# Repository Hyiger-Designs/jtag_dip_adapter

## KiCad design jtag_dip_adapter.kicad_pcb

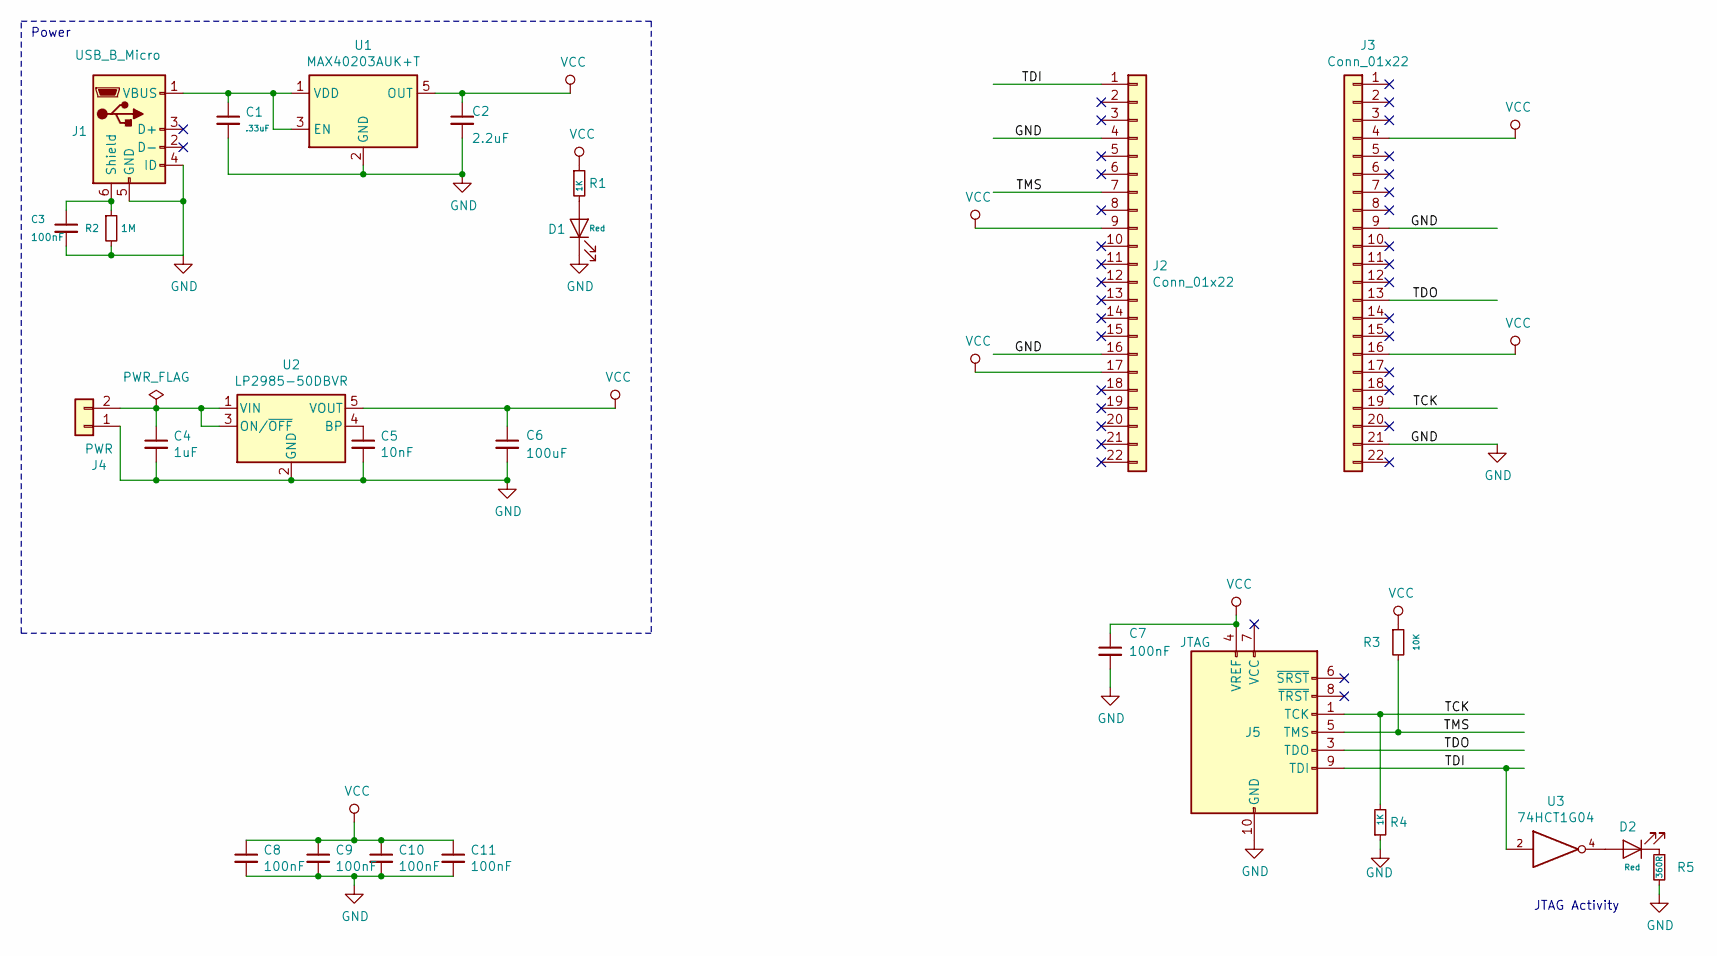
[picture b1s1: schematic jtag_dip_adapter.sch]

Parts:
C1: .33uF; C_0603_1608Metric_Pad1.05x0.95mm_HandSolder; MPN JMK107B7474KA-T
C2: 2.2uF; C_0603_1608Metric_Pad1.05x0.95mm_HandSolder; MPN C0603C225K8RACTU
C3: 100nF; C_0603_1608Metric_Pad1.05x0.95mm_HandSolder; MPN CC0603JRX7R9BB104
C4: 1uF; C_0603_1608Metric_Pad1.05x0.95mm_HandSolder
C5: 10nF; C_0603_1608Metric_Pad1.05x0.95mm_HandSolder
C6: 100uF; C_1206_3216Metric_Pad1.42x1.75mm_HandSolder
C7: 100nF; C_0603_1608Metric_Pad1.05x0.95mm_HandSolder; MPN JMK107B7474KA-T
C8, C9, C10, C11: 100nF; C_0603_1608Metric_Pad1.05x0.95mm_HandSolder
D1: Red; LED_0603_1608Metric_Pad1.05x0.95mm_HandSolder; MPN APT1608EC
D2: Red; LED_0603_1608Metric_Pad1.05x0.95mm_HandSolder
J1: USB_B_Micro; USB_Micro-B_Amphenol_10103594-0001LF_Horizontal; MPN 10103594-0001LF
J2, J3: Conn_01x22; PinSocket_1x22_P2.54mm_Vertical
J4: PWR; PinHeader_1x02_P2.54mm_Horizontal
J5: JTAG; Multicomp_MC9A12-1034_2x05_P2.54mm_Vertical
R1: 1K; R_0603_1608Metric_Pad1.05x0.95mm_HandSolder; MPN CR0603-FX-3600ELF
R2: 1M; R_0603_1608Metric_Pad1.05x0.95mm_HandSolder; MPN CR0603-FX-1004ELF
R3: 10K; R_0603_1608Metric_Pad1.05x0.95mm_HandSolder
R4: 1K; R_0603_1608Metric_Pad1.05x0.95mm_HandSolder
R5: 360R; R_0603_1608Metric_Pad1.05x0.95mm_HandSolder
U1: MAX40203AUK+T; SOT-23-5_HandSoldering; MPN MAX40203AUK+T
U2: LP2985-50DBVR; SOT-23-5_HandSoldering
U3: 74HCT1G04; TSOP-5_1.65x3.05mm_P0.95mm

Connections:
/TCK: J3.19, J5.1 (TCK), R4.2
/TDI: J2.1, J5.9 (TDI), U3.2
/TDO: J3.13, J5.3 (TDO)
/TMS: J2.7, J5.5 (TMS), R3.2
GND: C1.2, C2.2, C3.2, C4.2, C5.2, C6.2, C7.2, C8.2, C9.2, C10.2, C11.2, D1.1 (K), J1.4 (ID), J1.5 (GND), J2.4, J2.16, J3.9, J3.21, J4.1, J5.2 (GND), J5.10 (GND), R2.2, R4.1, R5.2, U1.2 (GND), U2.2 (GND), U3.3 (GND)
unnamed: C1.1, J1.1 (VBUS), U1.1 (VDD), U1.3 (EN)
unnamed: C3.1, J1.6 (Shield), R2.1
unnamed: C4.1, J4.2, U2.1 (VIN), U2.3 (ON/~OFF~)
unnamed: C5.1, U2.4 (BP)
unnamed: D1.2 (A), R1.2
unnamed: D2.1 (K), R5.1
unnamed: D2.2 (A), U3.4
VCC: C2.1, C6.1, C7.1, C8.1, C9.1, C10.1, C11.1, J2.9, J2.17, J3.4, J3.16, J5.4 (VREF), R1.1, R3.1, U1.5 (OUT), U2.5 (VOUT), U3.5 (VCC)

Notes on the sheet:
JTAG Activity
Power

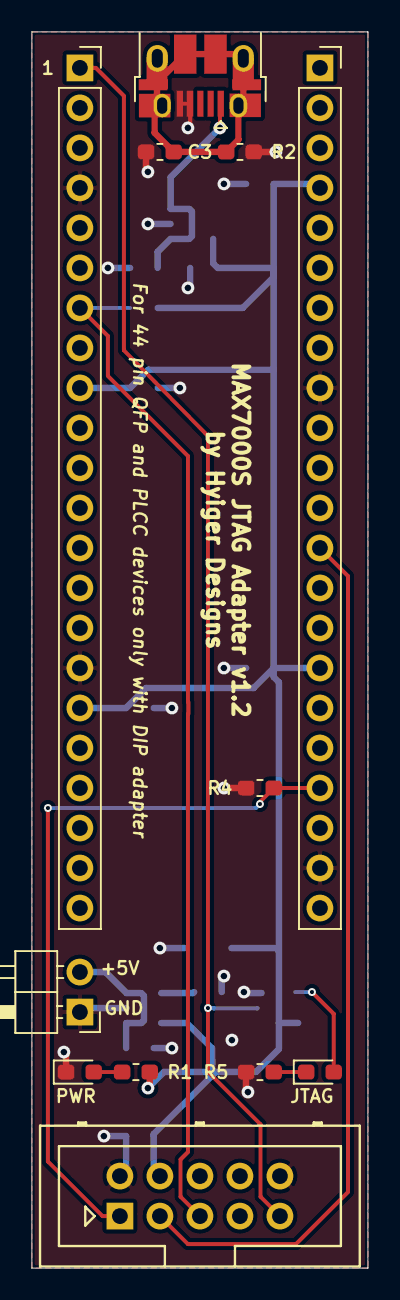
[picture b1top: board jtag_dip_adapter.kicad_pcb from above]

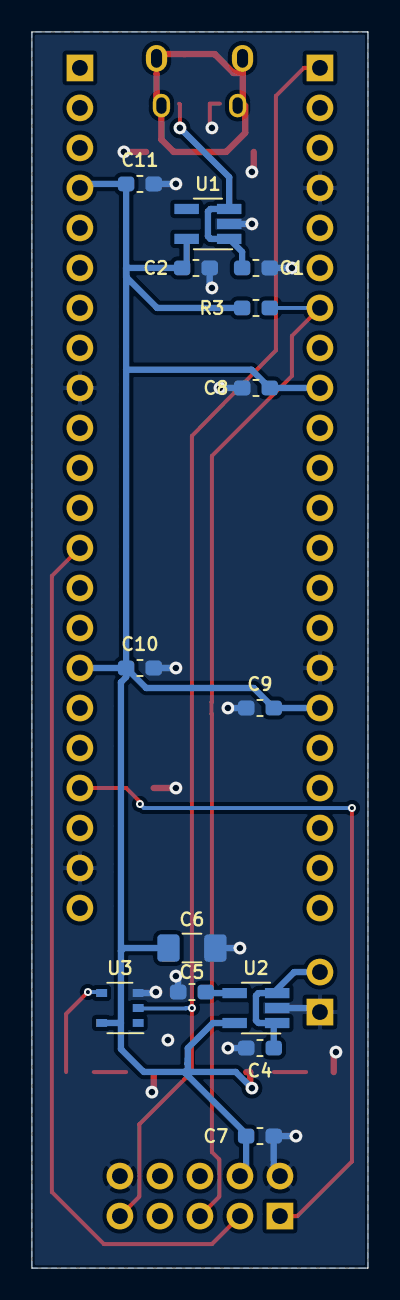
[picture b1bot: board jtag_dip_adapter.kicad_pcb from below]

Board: 2 copper layers, 21.3 x 78.5 mm, 26 parts (14 on the bottom side), 13 nets.

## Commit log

2019-10-31 first layout
2019-10-31 initial layout
2019-10-31 finished routing and silkscreen
2019-11-03 added 5V ldo reg
2019-12-19 removed extra capacitor and vias
